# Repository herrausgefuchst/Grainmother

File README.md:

# GRAINMOTHER

A Multi-Effect Audio Engine based on the BELA Platform

Grainmother is a multi-effect audio engine built on the [**BELA**](https://bela.io) platform. It’s designed for musicians and sound designers who want to create unique sounds without relying on external software. The project combines granular synthesis, reverb, and ring modulation into a single device controlled hands-on, rather than through traditional pedal interfaces.

The goal of Grainmother is to provide a flexible, standalone effects processor optimized for live performances. Leveraging BELA’s real-time audio processing capabilities and a custom hardware interface, it offers intuitive controls for creative experimentation.

This project is fully open-source, with all code and schematics available for those interested in exploring or building upon the device.

## Features

Grainmother features three distinct audio effects, each designed to provide unique sound-shaping capabilities. 

The **Ring Modulator** combines the input signal with a carrier signal, using analog simulations such as diode-based, transistor-based, and hybrid approaches. An additional LFO modulates the carrier signal, while bit crushing and noise modulation extend the effect. This allows for a range of sounds, from lush amplitude modulation to extremely harsh, crushed noise.

The **Granulator** breaks audio into short grains ranging from 1 to 100 milliseconds. In addition to standard controls like Grain Length and Density, properties such as panning and length can be randomized. A delay, dynamic feedback, and filtering options provide powerful tools for intricate sound design. This versatile set of parameters enables everything from subtle enhancements to fragmented, evolving soundscapes.

The **Reverb** delivers a rich spatial effect by blending early reflections with a late reverberation algorithm inspired by Schroeder and Moorer. Selectable types, including Church, Digital Vintage, Seasick, and Room, allow users to craft immersive spaces and fine-tune parameters such as decay, pre-delay, and modulation. A unique feature is the feedback loop within the early reflection algorithm: lower values increase echo density artificially, while higher values create unique, morphing sounds.

The three effects can be processed in either **parallel** or **series** mode, with the user having the ability to define the processing order. Each effect features an individual Mix/Wet control, along with a master control for the entire effect engine. All processing is done **true stereo**. 

A dedicated **menu**, accessible via four buttons, allows for additional settings such as potentiometer behavior, MIDI input and output channels, and advanced effect parameters.

An **OLED display** provides real-time feedback, showing parameter changes and navigating the menu.

The Grainmother includes a built-in **preset system** that allows users to save and recall custom effect configurations. This feature provides quick access to stored settings, making it ideal for maintaining consistency during live performances or efficiently switching between sounds.

The device supports **full MIDI integration** via the Mini-USB connector on the side. Parameters can be controlled using Control Change messages, and presets can be switched using Program Change messages from external MIDI devices. Additionally, the eight potentiometers can function as MIDI controllers, sending out Control Change messages for further flexibility.

## Documentation

See the full documentation of the code [here](http://julianfuchs.ch/grainmother).

## License

This project is licensed under the [Creative Commons Attribution-NonCommercial-ShareAlike 4.0 International License](https://creativecommons.org/licenses/by-sa/4.0/).

## How tu Use

I would be very happy to share further insights into my concepts and designs with you. Please feel free to reach out to me for more information. Additionally, if you are interested in the product, I would be pleased to create a custom device tailored to your needs.

For inquiries, please visit: [www.julianfuchs.ch](https://www.julianfuchs.ch)

## References

- **BELA.** 2024. [bela.io](https://bela.io)
- **Bencina, Ross.** 2001. *Implementing Real-Time Granular Synthesis.*
- **Dahl, Luke, and Jean-Marc Jot.** 2000. *A Reverberator Based on Absorbent All-Pass Filters.* Proceedings of the COST G-6 Conference on Digital Audio Effects (DAFX-00).
- **Dattorro, Jon.** 1997. *Effect Design, Part 1: Reverberator and Other Filters.* Journal of the Audio Engineering Society.
- **Hoffmann-Burchardi, Richard.** 2009. *Asymmetries Make the Difference: An Analysis of Transistor-Based Analog Ring Modulators.* Proc. of the 12th Int. Conference on Digital Audio Effects. Como, Italy.
- **Moorer, James A.** 1978. *About This Reverberation Business.* Computer Music Journal.
- **Opie, Tallaine.** 2024. *Granular Synthesis.* [granularsynthesis.com](http://www.granularsynthesis.com/). Accessed October 21, 2024.
- **Parker, Julian.** 2011. *A Simple Digital Model of the Diode-Based Ring-Modulator.* Proc. of the 14th International Conference on Digital Audio Effects. Paris, France.
- **Pirkle, Will C.** 2017. *Designing Audio Effect Plugins in C++.* New York: Routledge.
- **Pirkle, Will.** 2013. *Virtual Analog 2nd Order Moog Half-Ladder Filter - App Note 8.*
- **Schroeder, Manfred R.** 1962. *Natural Sounding Artificial Reverberation.* Journal of the Audio Engineering Society.
- **Truax, Barry.** 1988. *Real-Time Granular Synthesis with a Digital Signal Processor.* Computer Music Journal, Vol. 12, No. 2.
- **Välimäki, V., J. Parker, L. Savioja, J. O. Smith, and J. S. Abel.** 2012. *Fifty Years of Artificial Reverberation.* IEEE Transactions on Audio, Speech, and Language Processing, Vol. 20, No. 5.
- **Valhalla.** 2024. [Valhalla DSP](https://valhalladsp.com). Accessed December 31, 2024.

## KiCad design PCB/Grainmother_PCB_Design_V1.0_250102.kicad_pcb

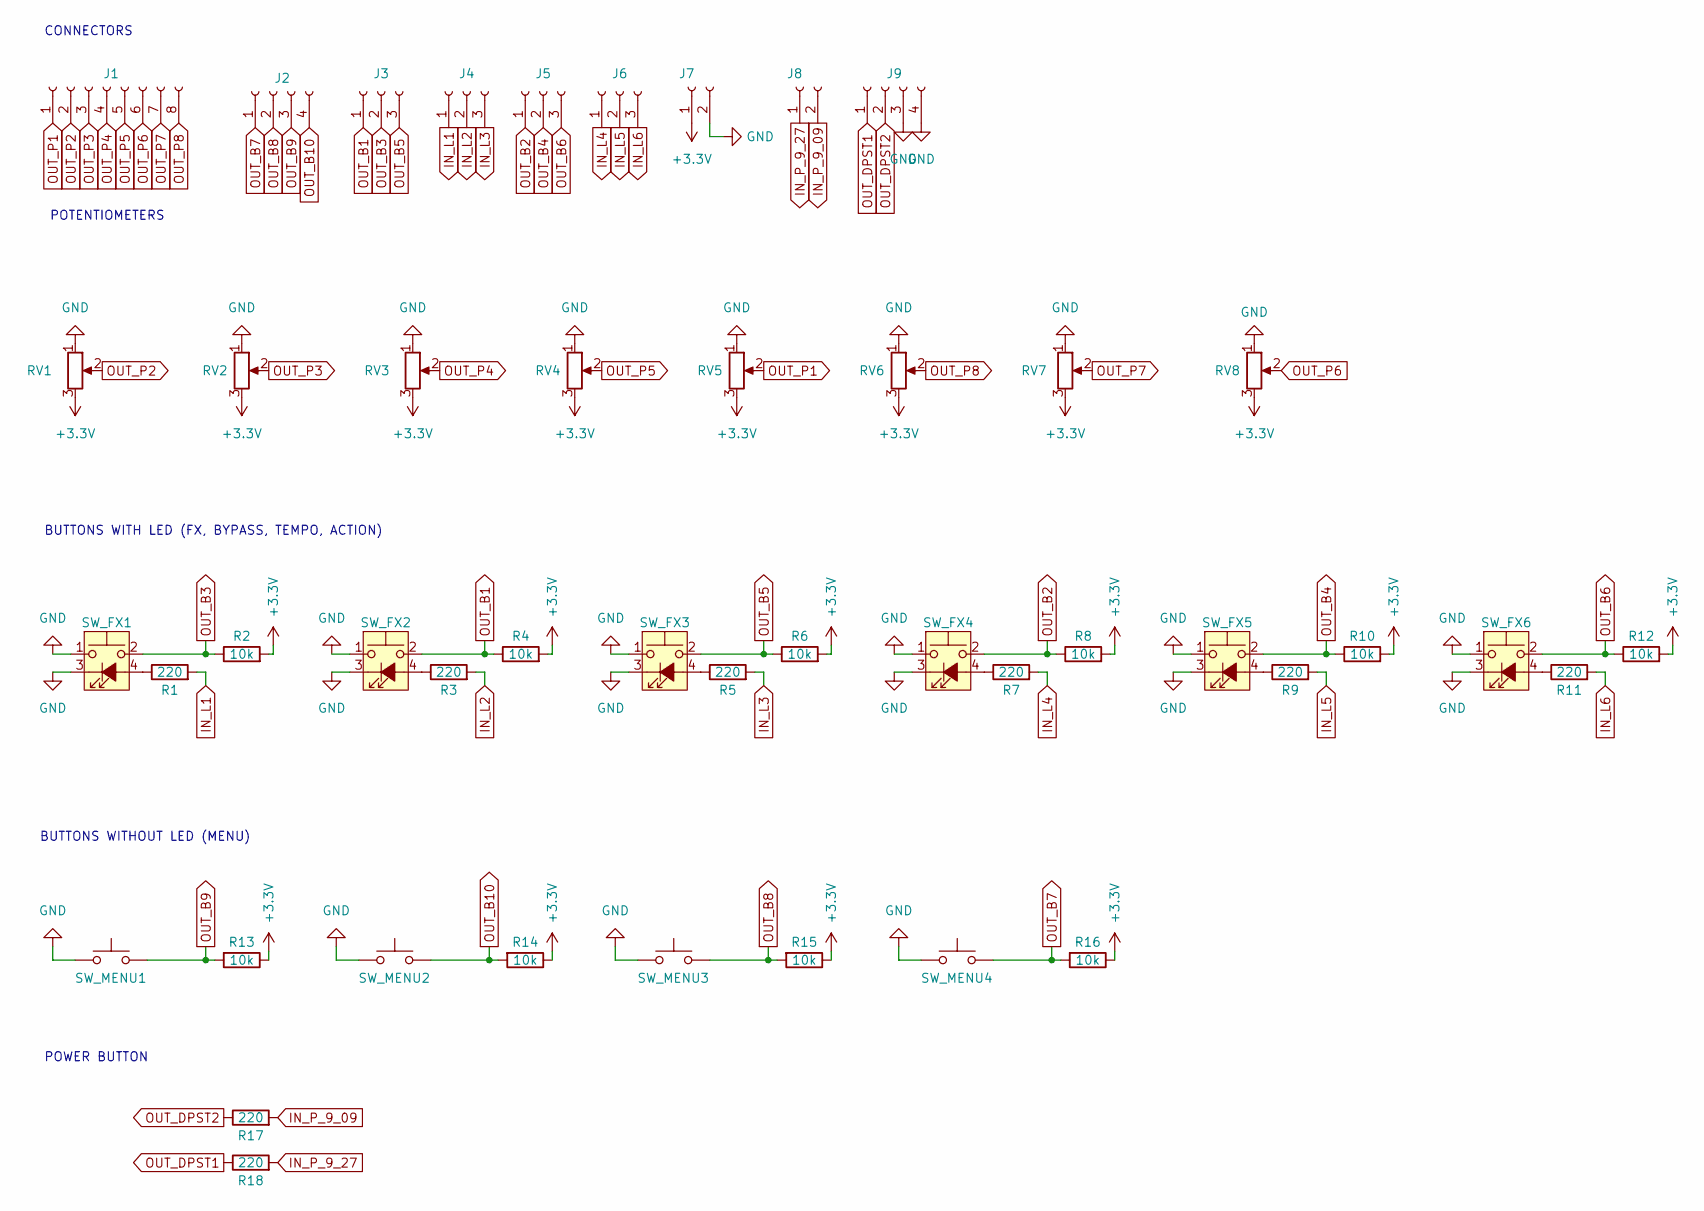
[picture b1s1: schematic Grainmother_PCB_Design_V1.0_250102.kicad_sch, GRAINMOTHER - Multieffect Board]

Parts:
J1: CONN_22-27-2081_MOL
J2, J9: Conn_01x04_Socket; CONN_22-27-2041_MOL
J3, J4, J5, J6: Conn_01x03_Socket; CONN_22292031_MOL
J7, J8: Conn_01x02_Socket; CONN_22-27-2021_MOL
R1, R3, R5, R7, R9, R11, R17, R18: 220; R_Axial_DIN0207_L6.3mm_D2.5mm_P10.16mm_Horizontal
R2, R4, R6, R8, R10, R12, R13, R14, R15, R16: 10k; R_Axial_DIN0207_L6.3mm_D2.5mm_P10.16mm_Horizontal
RV1, RV2, RV3, RV4, RV5, RV6, RV7, RV8: Potentiometer_Bourns_PTV111-3_Vertical
SW_FX1, SW_FX2, SW_FX3, SW_FX4, SW_FX5, SW_FX6: SW_Push_LED; SW-DIGITAST_NarrowSpacing_LeftSided
SW_MENU1, SW_MENU2, SW_MENU3, SW_MENU4: SW-DIGITAST_NarrowSpacing_noLED_LeftSided

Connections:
+3.3V: J7.1, R2.2, R4.2, R6.2, R8.2, R10.2, R12.2, R13.1, R14.1, R15.1, R16.1, RV1.3, RV2.3, RV3.3, RV4.3, RV5.3, RV6.3, RV7.3, RV8.3
GND: J7.2, J9.3, J9.4, RV1.1, RV2.1, RV3.1, RV4.1, RV5.1, RV6.1, RV7.1, RV8.1, SW_FX1.1, SW_FX1.3 (K), SW_FX2.1, SW_FX2.3 (K), SW_FX3.1, SW_FX3.3 (K), SW_FX4.1, SW_FX4.3 (K), SW_FX5.1, SW_FX5.3 (K), SW_FX6.1, SW_FX6.3 (K), SW_MENU1.1, SW_MENU2.1, SW_MENU3.1, SW_MENU4.1
IN_L1: J4.1, R1.2
IN_L2: J4.2, R3.2
IN_L3: J4.3, R5.2
IN_L4: J6.1, R7.2
IN_L5: J6.2, R9.2
IN_L6: J6.3, R11.2
IN_P_9_09: J8.2, R17.2
IN_P_9_27: J8.1, R18.2
unnamed: R1.1, SW_FX1.4 (A)
unnamed: R3.1, SW_FX2.4 (A)
unnamed: R5.1, SW_FX3.4 (A)
unnamed: R7.1, SW_FX4.4 (A)
unnamed: R9.1, SW_FX5.4 (A)
unnamed: R11.1, SW_FX6.4 (A)
OUT_B1: J3.1, R4.1, SW_FX2.2
OUT_B2: J5.1, R8.1, SW_FX4.2
OUT_B3: J3.2, R2.1, SW_FX1.2
OUT_B4: J5.2, R10.1, SW_FX5.2
OUT_B5: J3.3, R6.1, SW_FX3.2
OUT_B6: J5.3, R12.1, SW_FX6.2
OUT_B7: J2.1, R16.2, SW_MENU4.2
OUT_B8: J2.2, R15.2, SW_MENU3.2
OUT_B9: J2.3, R13.2, SW_MENU1.2
OUT_B10: J2.4, R14.2, SW_MENU2.2
OUT_DPST1: J9.1, R18.1
OUT_DPST2: J9.2, R17.1
OUT_P1: J1.1, RV5.2
OUT_P2: J1.2, RV1.2
OUT_P3: J1.3, RV2.2
OUT_P4: J1.4, RV3.2
OUT_P5: J1.5, RV4.2
OUT_P6: J1.6, RV8.2
OUT_P7: J1.7, RV7.2
OUT_P8: J1.8, RV6.2

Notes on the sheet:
BUTTONS WITH LED (FX, BYPASS, TEMPO, ACTION)
POTENTIOMETERS
POWER BUTTON
CONNECTORS
BUTTONS WITHOUT LED (MENU)

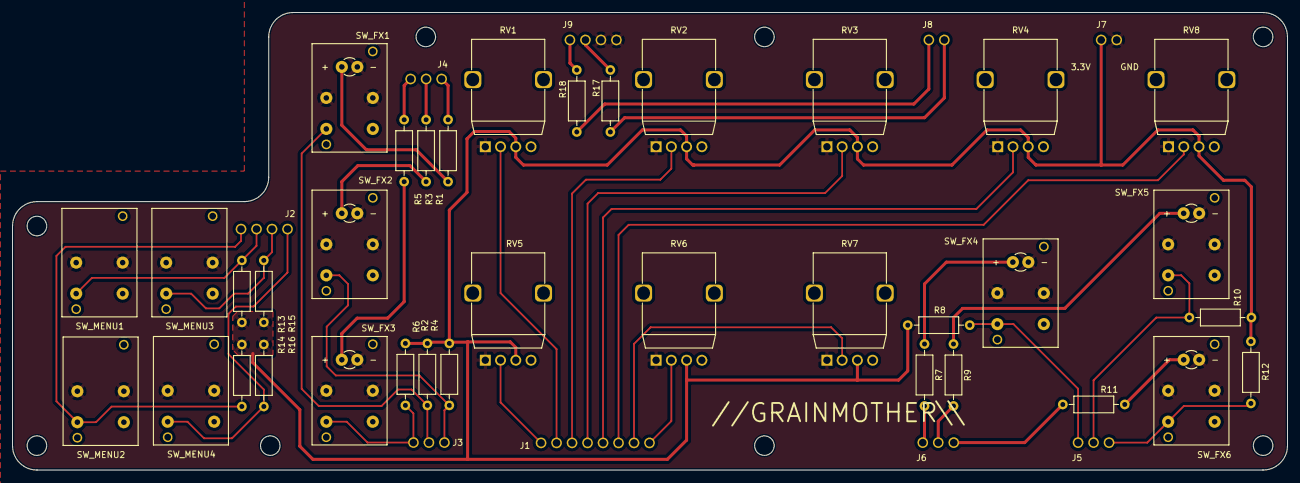
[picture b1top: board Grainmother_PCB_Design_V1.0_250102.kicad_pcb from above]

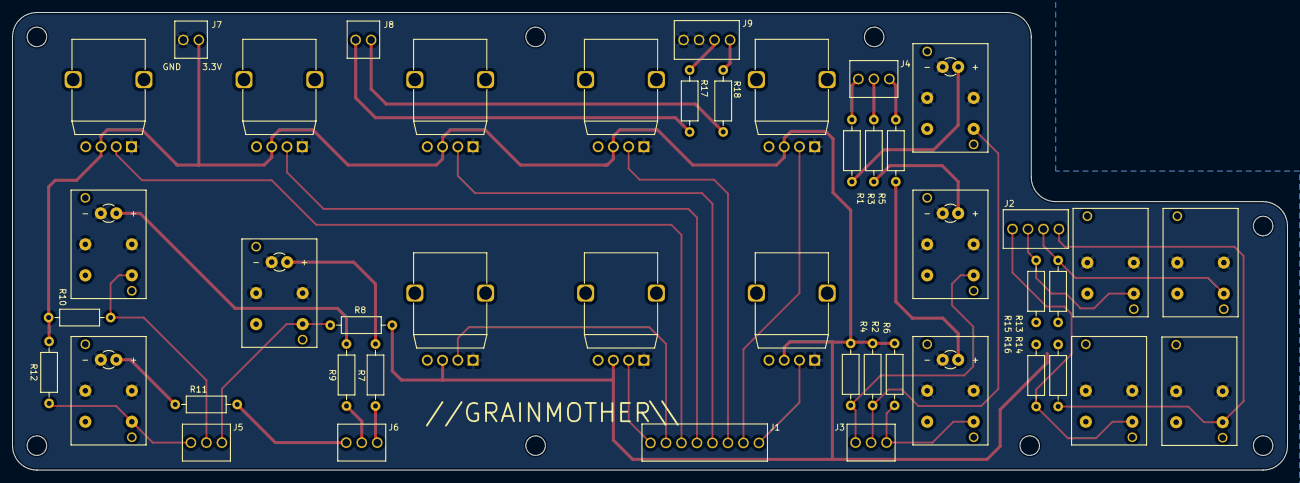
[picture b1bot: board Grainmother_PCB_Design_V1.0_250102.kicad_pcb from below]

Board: 2 copper layers, 209.0 x 75.0 mm, 45 parts (9 on the bottom side), 36 nets.

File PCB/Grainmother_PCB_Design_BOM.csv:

"#","Reference","Qty","Value","Footprint","DNP"
"1","J1","1","~","Custom Parts:CONN_22-27-2081_MOL",""
"2","J2, J9","2","Conn_01x04_Socket","Custom Parts:CONN_22-27-2041_MOL",""
"3","J3, J4, J5, J6","4","Conn_01x03_Socket","Custom Parts:CONN_22292031_MOL",""
"4","J7, J8","2","Conn_01x02_Socket","Custom Parts:CONN_22-27-2021_MOL",""
"5","R1, R3, R5, R7, R9, R11, R17, R18","8","220","Resistor_THT:R_Axial_DIN0207_L6.3mm_D2.5mm_P10.16mm_Horizontal",""
"6","R2, R4, R6, R8, R10, R12, R13, R14, R15, R16","10","10k","Resistor_THT:R_Axial_DIN0207_L6.3mm_D2.5mm_P10.16mm_Horizontal",""
"7","RV1, RV2, RV3, RV4, RV5, RV6, RV7, RV8","8","~","Custom Parts:Potentiometer_Bourns_PTV111-3_Vertical",""
"8","SW_FX1, SW_FX2, SW_FX3, SW_FX4, SW_FX5, SW_FX6","6","SW_Push_LED","Custom Parts:SW-DIGITAST_NarrowSpacing_LeftSided",""
"9","SW_MENU1, SW_MENU2, SW_MENU3, SW_MENU4","4","~","Custom Parts:SW-DIGITAST_NarrowSpacing_noLED_LeftSided",""

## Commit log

2024-08-05 initial state
2024-08-15 rearranged constantvariables and fucntions, StereoFloat instead of FloatPair, effects.h slighty changed, documentation functions
2024-08-15 document and beatuty work for Potentiometer and UI Element
2024-08-15 clean and document Button class
2024-08-15 fixes, programm not running
2024-08-15 further cleaning, step by step approach
2024-08-16 comment everything not needed now
2024-08-16 killed moving averager from potentiometer
2024-08-16 potentiometer analog value scaling
2024-08-16 created new file for engine parameters
2024-08-16 clean up ui elements, document classes, define for GUI connection
2024-08-16 documentation and small changes to audioengine
2024-08-16 rearranged engine parameters
2024-08-16 comment change
2024-08-16 documented parameters.h changed some function names
2024-08-17 a massive load of changes in parameters
2024-08-18 basic functionality ui elements to parameters works!
2024-08-18 effect edit focus control works, setup of reverb parameters
2024-08-18 leds connected and work, added placeholder granulator variables, effect edit focus seems to work
2024-08-19 userinterface update in a separate thread
2024-08-19 added menu basic
2024-08-19 added parameter page for menu
2024-08-19 added a navigation page in menu
2024-08-19 added global settings as a new audio parameter group
2024-08-19 deleted the program parameters again and added them to the menu
2024-08-19 killed global parameters
2024-08-19 added listener userinterface to menu for setting global settings
2024-08-19 killed items in Menu::Page
2024-08-19 cleaned Menu class a little bit
2024-08-19 implemented Loading preset from JSON, should work, but didnt test on BELA
2024-08-19 trying to add save preset
2024-08-20 added scrol functio to menu adio parameters
2024-08-20 added parameter and menu control for effect order, rearranged menu files, save page now copys value from load page
2024-08-20 combined addPage with template arguments, made Default not overwriteable
2024-08-20 beauty changes, name changes
2024-08-20 when reentering menu, always start on same menu index
2024-08-20 global settings only change when enter is pressed
2024-08-20 finished commenting menu cpp, rearranged constructors for some page classes
2024-08-20 rearranged LED, fixed problem with stuck in alert mode
2024-08-20 action led now blinks when potentiometer catched the value
2024-08-21 commented LED
2024-08-21 changed names and style of display class
2024-08-21 added the original display
2024-08-21 cleaned print(display function in menu, call to display over std::function
2024-08-21 menu can now differentiate ui parameters and menu parameters
2024-08-21 display owns a pointer to the preset page
2024-08-21 ui parameters can be nudged by up and down buttons
2024-08-21 display osc transmitter works! rearranged userinterface class
2024-08-21 on long press of enter, the current ui parameter will now be reset to default
2024-08-22 fixed todo for the display, pot touches now also trigger the display
2024-08-22 tampo tapper included
2024-08-22 tempo led reacts to tempo parameter
2024-08-22 bugfix with metronome and led
2024-08-23 tempo sets parameters
2024-08-23 documentation of parameters, combined addParameter of AudioParmaeterGroup
2024-08-23 cleaned up LED class
2024-08-23 cleaned up display class
2024-08-23 fixed bug with display when initializing
2024-08-23 show loaded preset on display on start of program
2024-08-23 pot catch value works, small bug fixes to menu hierarchy
2024-08-23 algorithm for definable effect order
2024-08-23 advanced effect order algorithm (bypassed effects)
2024-08-25 documentation for userinterface cpp, bug fixes
2024-08-25 bug fix with parameter index
2024-08-25 led representing choice parameter shows logarithmic value
2024-08-25 small cleanup
2024-08-25 cleaned up listeners/lambda functions
2024-08-25 midi bela class included, receives message on fixed input channel
2024-08-25 added Reverb files
2024-08-25 include reverb object, not running...
2024-08-26 added reverb! added a subclass NamingPage in menu
2024-08-26 menu is able to name a preset
2024-08-26 killed Ramp in SlideParameter and confusion between print value and value
2024-08-27 killed out some console prints and comments
2024-08-27 extracted dry wet control from reverb effect, better control of effect engaging
2024-08-27 global bypass button included with ramps
2024-08-27 documentation Engine.h
2024-10-09 comments
2024-10-10 included granulator!
2024-10-11 mix/wetness control for parallel processing
2024-10-14 effect order and mix parameters changed
2024-10-15 changed wet/dry scaling and reverb highcut resonance
2024-10-15 added parameter granulator envelope type
2024-10-17 finetuned feedback control, added to ui controls for granulator
2024-10-17 small parameter changes
2024-11-28 small TODOs
2024-11-28 ringmodulation
2024-12-03 bitcrushing works now
2024-12-03 fine tune ringmod
2024-12-03 changed process functions to pass in float32x2_t
2024-12-03 killed some unnecessary classes
2024-12-03 tempo to effect parameters
2024-12-03 fixed global bypass
2024-12-03 killed unnecessary stuff, cleaned documentation
2024-12-04 documentation
2025-01-06 receives MIDI Program Change Messages
2025-01-07 fixed a mix problem
2025-01-09 changed effect order and bypass ramp fix
2025-01-09 asdf
2025-01-10 reverb changed early reflection ramp accress
2025-01-11 small changes
2025-01-12 midi CC messages input
2025-01-12 potentiometers send out midi cc messages
2025-01-14 reordering files
2025-01-14 readme
2025-01-14 excluding Xcode folder
2025-01-14 removed xcode
2025-01-14 doxygen
2025-01-14 docs again
2025-01-14 Manual
2025-01-14 enclosure
2025-01-14 pics
2025-01-14 pcb pics
2025-01-15 docs
2025-01-24 Code Documentation + Enclosure Files
